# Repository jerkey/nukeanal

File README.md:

#nukeanal
##nuclear analyzer pulse capture board
designed in KiCAD with Jerry Chamkis

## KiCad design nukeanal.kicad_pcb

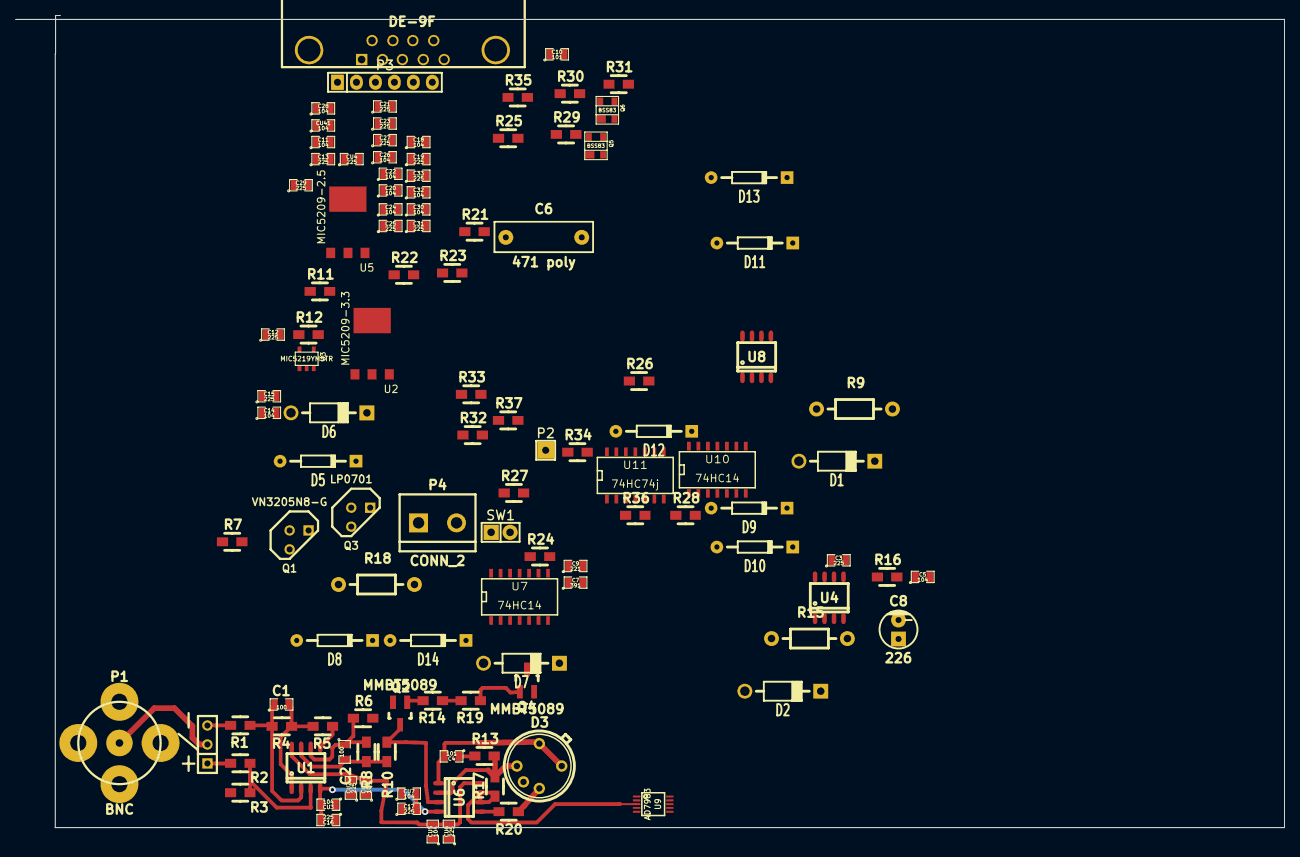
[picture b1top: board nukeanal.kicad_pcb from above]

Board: 2 copper layers, 169.9 x 108.7 mm, 115 parts (0 on the bottom side), 64 nets.

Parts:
+/-: CONN_3; SIL-3
C1, C2: 100; SM0805
C3, C12, C13, C15, C16, C17, C19, C21, C23, C25, C27, C29, C31, C33: 225; SM0805
C4, C10: 101; SM0805
C5, C11, C14, C18, C20, C22, C24, C26, C28, C30, C32: 104; SM0805
C6: 471 poly; Capacitor13x4RM10
C7: 391; SM0805
C8: 226; CP_5x6mm
C9: 221; SM0805
CU1, CU3, CU5, CU7, CU41: 104; SM0805
CU2, CU4, CU6: 225; SM0805
D1, D2: 1N5819; Diode_DO-41_SOD81_Horizontal_RM10
D3: DPAD1; TO-78_Housing_5Pin
D5: 6.2V; Diode_DO-35_SOD27_Horizontal_RM10
D6, D7: 1N4007; Diode_DO-41_SOD81_Horizontal_RM10
D8, D9, D10, D11, D12, D13, D14: 1N4148; Diode_DO-35_SOD27_Horizontal_RM10
P1: BNC; bnc-rocket
P2: CONN_1; testpin037
P3: CONN_6; 6x1pin037
P4: CONN_2; bornier2
P5: DE-9F; DB9FC
Q1: VN3205N8-G; TO92DGS
Q2, Q4: MMBT5089; SOT23_Transistor_BC846_Handsoldering_RevB_14Mar2014
Q3: LP0701; TO92DGS
Q5, Q6: BSS83; sot143B
R1: 30K; Resistor_SMD0805_HandSoldering
R2, R25: 3K; Resistor_SMD0805_HandSoldering
R3, R4: 27K; Resistor_SMD0805_HandSoldering
R5: 240; Resistor_SMD0805_HandSoldering
R6, R32, R33, R35, R37: 100; Resistor_SMD0805_HandSoldering
R7: 22M; Resistor_SMD0805_HandSoldering
R8, R10, R14, R17, R19: 1K; Resistor_SMD0805_HandSoldering
R9: 10-30 for -.5V; Resistor_Horizontal_RM10mm
R11: 422705; Resistor_SMD0805_HandSoldering
R12: 100K; Resistor_SMD0805_HandSoldering
R13, R26, R27, R28: 200; Resistor_SMD0805_HandSoldering
R15: SEL O.S.; Resistor_Horizontal_RM10mm
R16, R30: 1k; Resistor_SMD0805_HandSoldering
R18: SEL FOR LOWBATT SHUTOFF; Resistor_Horizontal_RM10mm
R20, R21, R23: 47; Resistor_SMD0805_HandSoldering
R22, R24, R34: 10k; Resistor_SMD0805_HandSoldering
R29, R31: 1M; Resistor_SMD0805_HandSoldering
R36: 10K; Resistor_SMD0805_HandSoldering
SW1: ONOFF; Pin_Header_Straight_1x02
U1, U6: OPA2365; SO-8
U2: MIC5209-3.3; SOT-223-3
U3: MIC5219YM5TR; SOT23-5
U4: REF5045; SO-8
U5: MIC5209-2.5; SOT-223-3
U7, U10: 74HC14; SO14N
U8: LM311N; SO-8
U9: AD7983; MSOP10-0.5
U11: 74HC74j; SO14N

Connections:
+2.5V: C24.2, C25.2, C30.2, C31.2, U5.3, U9.2
+3.3V: C18.2, C19.2, C20.2, C21.2, C22.2, C23.2, C26.2, C27.2, C32.2, C33.2, D8.2, D9.2, D10.2, D12.2, D14.2, R22.1, R24.1, R25.1, R34.2, R36.1, U2.3, U7.14, U9.9, U9.10, U10.14, U11.1, U11.2, U11.3, U11.4, U11.14
+5.25V: C11.2, C13.2, C28.2, C29.2, CU1.2, CU2.2, CU4.1, CU5.2, CU6.2, CU41.2, R11.1, U1.8, U3.5, U4.2, U5.1, U6.8, U8.8
-0.5V: C14.2, C15.2, Q1.D, R9.2, U8.4
-0.25V: C16.2, C17.2, CU3.2, CU7.2, D1.1, D2.2, U1.4, U6.4
/BATT+: D6.2, P4.1, Q3.S, R18.1, U2.1, U3.3
/BATT--: P4.2, SW1.1
/REF45: C8.1, R15.2, U4.6, U9.1
/SCLK: P3.4, P5.7, R33.1
/SDO: P3.3, P5.6, R32.1
/TEST: P2.1, R34.1, U11.13
/X: D11.2, D13.2, R14.1, R19.2
/~CE: P3.5, P5.8, R37.1
/~REQ: P3.6, P5.9, R35.1
GND: C3.1, C5.2, C6.2, C7.1, C8.2, C10.1, C11.1, C12.1, C13.1, C14.1, C15.1, C16.1, C17.1, C18.1, C19.1, C20.1, C21.1, C22.1, C23.1, C24.1, C25.1, C26.1, C27.1, C28.1, C29.1, C30.1, C31.1, C32.1, C33.1, CU1.1, CU2.1, CU3.1, CU4.2, CU5.1, CU6.1, CU7.1, CU41.1, D2.1, D6.1, D7.2, P1.2, P3.1, P3.2, P5.1, P5.2, P5.3, P5.4, P5.5, Q2.E, Q4.E, Q5.2, Q6.2, R3.1, R6.2, R12.1, R16.2, R29.1, R31.1, U2.2, U3.2, U4.4, U5.2, U7.1, U7.3, U7.5, U7.7, U8.1, U9.4, U9.5, U10.7, U11.7, U11.12
unnamed: C1.1, R1.1, R4.2, U1.2
unnamed: C1.2, R4.1, R5.2, U1.1
unnamed: C2.1, R6.1, R8.2, U1.6
unnamed: C2.2, R8.1, R10.2, U1.7
unnamed: C3.2, U4.5
unnamed: C4.1, R13.1
unnamed: C4.2, D3.1, D3.7, U6.1
unnamed: C5.1, R15.1, R16.1, U8.2
unnamed: C6.1, R20.2, R21.2, U6.5
unnamed: C7.2, R23.1, U7.9
unnamed: C9.1, U7.8
unnamed: C9.2, D8.1, R24.2, U7.11
unnamed: C10.2, R30.1, U10.9
unnamed: C12.2, R11.2, R12.2, U3.4
unnamed: D1.2, R9.1
unnamed: D3.2, R13.2, R17.2, U6.2
unnamed: D3.5, R20.1
unnamed: D5.1, D7.1, Q1.S, R7.2, SW1.2
unnamed: D5.2, Q3.G, R18.2
unnamed: D9.1, R32.2, U10.4
unnamed: D10.1, R33.2, U10.5
unnamed: D11.1, U11.8
unnamed: D12.1, R35.2, U11.9
unnamed: D13.1, Q6.4, R31.2, U10.12
unnamed: D14.1, R36.2, R37.2, U10.13, U11.10
unnamed: +/-.1, R2.2
unnamed: +/-.2, P1.1
unnamed: +/-.3, R1.2
unnamed: Q1.G, Q3.D, R7.1
unnamed: Q2.B, R14.2
unnamed: Q2.C, R10.1, U6.3, U8.3
unnamed: Q4.B, R19.1
unnamed: Q4.C, R21.1
unnamed: Q5.3, Q6.3, R25.2, R26.2
unnamed: Q5.4, R29.2, R30.2, U7.10
unnamed: R2.1, R3.2, U1.3
unnamed: R5.1, U1.5
unnamed: R17.1, U6.6, U6.7, U9.3
unnamed: R22.2, R23.2, U8.7
unnamed: R26.1, U9.6
unnamed: R27.1, U9.7
unnamed: R27.2, U7.13
unnamed: R28.1, U9.8
unnamed: R28.2, U10.2
unnamed: U8.5, U8.6
unnamed: U10.1, U10.6
unnamed: U7.12, U10.3
unnamed: U10.10, U11.11
unnamed: U10.8, U10.11

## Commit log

2014-04-06 nukeanal first commit
2014-04-06 added .PDF of schematic
2014-04-09 working on assigning footprints
2014-04-10 finished with schematic, footprint assignment, but no board yet
2014-04-10 fixed library representation of DPAD1
2014-04-10 jerry fixed regulator
2014-04-10 add SOT-223-3 footprint
2014-04-10 add TO-78 5-pin footprint
2014-04-10 add bnc-rocket footprint file
2014-04-10 leaving jerry to lay out the board, after autoplacing
2014-04-12 used a zip to force merge to jakes latest work
2014-07-20 moved some caps around
2016-03-24 add pictures and README.md
2016-03-31 updated schematic image with higher res
2018-12-12 updated schematic image
